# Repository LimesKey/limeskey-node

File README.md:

# parsnip-node
A battery-powered, portable Meshtastic/Meshcore node built around a Seeed XIAO ESP32-C6, an Ebyte E22P-915M30S LoRa front end, and a u-blox NEO-M9N GNSS receiver. Designed in KiCad, it targets 915 MHz operation in Canada under ISED RSS-247.

## Overview

The goal is a self-contained LoRa node that pairs one of the longest range, best value LoRa modules, with an accurate GNSS reciever, running off a single 18650 cell, to connect to other people on the LoRa mesh network community.

<table>
  <tr>
    <td align="center" width="33%">
      
      <br><sub><b>Assembled board</b></sub>
    </td>
    <td align="center" width="33%">
      
      <br><sub><b>Outdoor testing</b></sub>
    </td>
    <td align="center" width="33%">
      
      <br><sub><b>Outdoor testing, back</b></sub>
    </td>
  </tr>
</table>

## Hardware
 
| Function | Part | Notes |
| --- | --- | --- |
| MCU / radio host | Seeed XIAO ESP32-C6 | Used as an SMD/castellated module for easy soldering|
| LoRa | Ebyte E22P-915M30S | SX1262 + external PA, up to 30 dBm |
| GNSS | u-blox NEO-M9N | GPS / GLONASS / Galileo / BeiDou |
| Boost | TI TPS61033 |  |
| Power mux | TI TPS2116 | USB / battery source selection |
| Battery protection | TI BQ29700 | Single-cell protection |
| Reverse polarity | AO3401A P-channel MOSFET | Input protection |
| Cell | 18650 3500mAh Li-ion | Single cell |
 
### Board
 
- 4-layer, 55 x 100 mm
- JLCPCB `JLC04161H-7628` stackup, 1 oz copper
- L1-L2 prepreg 0.2104 mm, Dk 4.4
- RF: 0.36mm trace width for ~50 Ω CPWG on this stackup, ground rails stitched with 0.3 mm / 0.6 mm vias at roughly 1.5 to 2 mm pitch
  
### SX1262 to ESP32-C6 pin map
 
| Signal | GPIO |
| --- | --- |
| NSS | 21 |
| SCK | 19 |
| MISO | 20 |
| MOSI | 18 |
| DIO1 | 1 |
| BUSY | 7 |
| NRST | 16 |
| EN | 17 |
 
The E22P `EN` (module pin 6) is held high for both RX and TX. The T/R switch (pin 7) is driven automatically from the SX1262 DIO2 line, so the firmware sets `setDio2AsRfSwitch(true)`.
 
## Firmware
 
Firmware is a Meshtastic fork tracked as the `firmware` submodule ([LimesKey/firmware](https://github.com/LimesKey/firmware)). Development uses VS Code with the pioarduino extension, which Meshtastic pins for ESP32-C6 / Arduino-ESP32 3.x support. A device variant declares the pin map above and the PA control lines so TX actually keys up. Unfortunately there are some extensive changes to the Meshtastic firmware in order to incorporate a SPI GNSS module, as this is not natively supported by Meshtastic.
 
```bash
git clone --recurse-submodules https://github.com/LimesKey/parsnip-node.git
```

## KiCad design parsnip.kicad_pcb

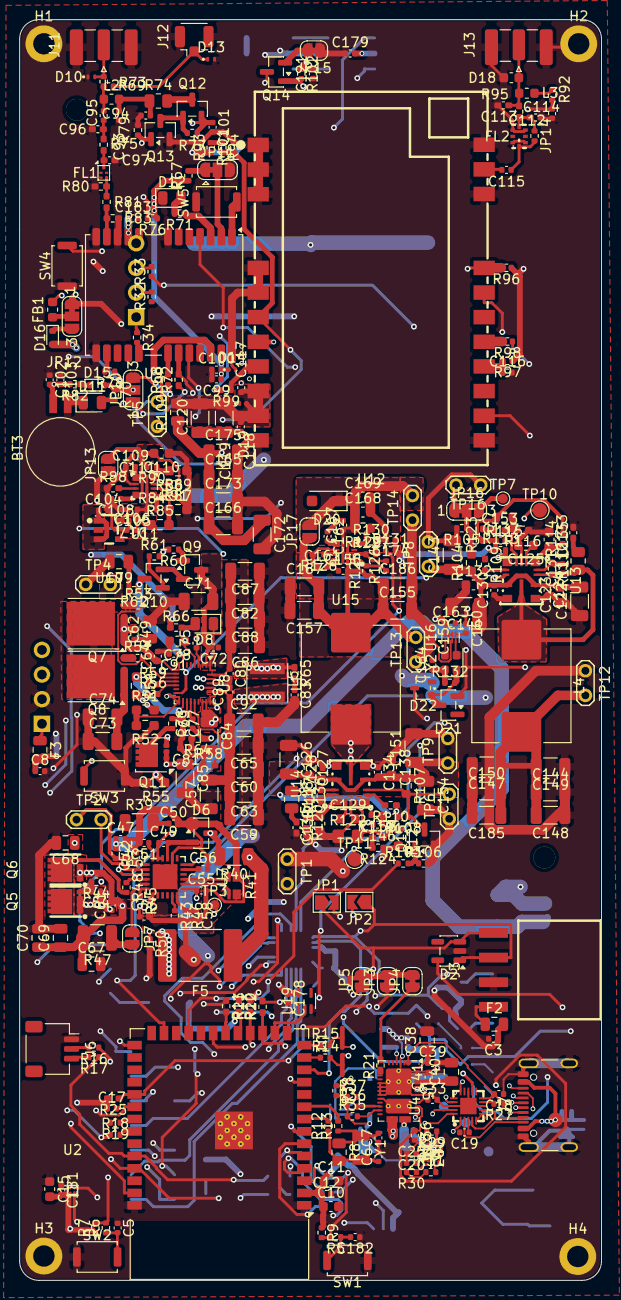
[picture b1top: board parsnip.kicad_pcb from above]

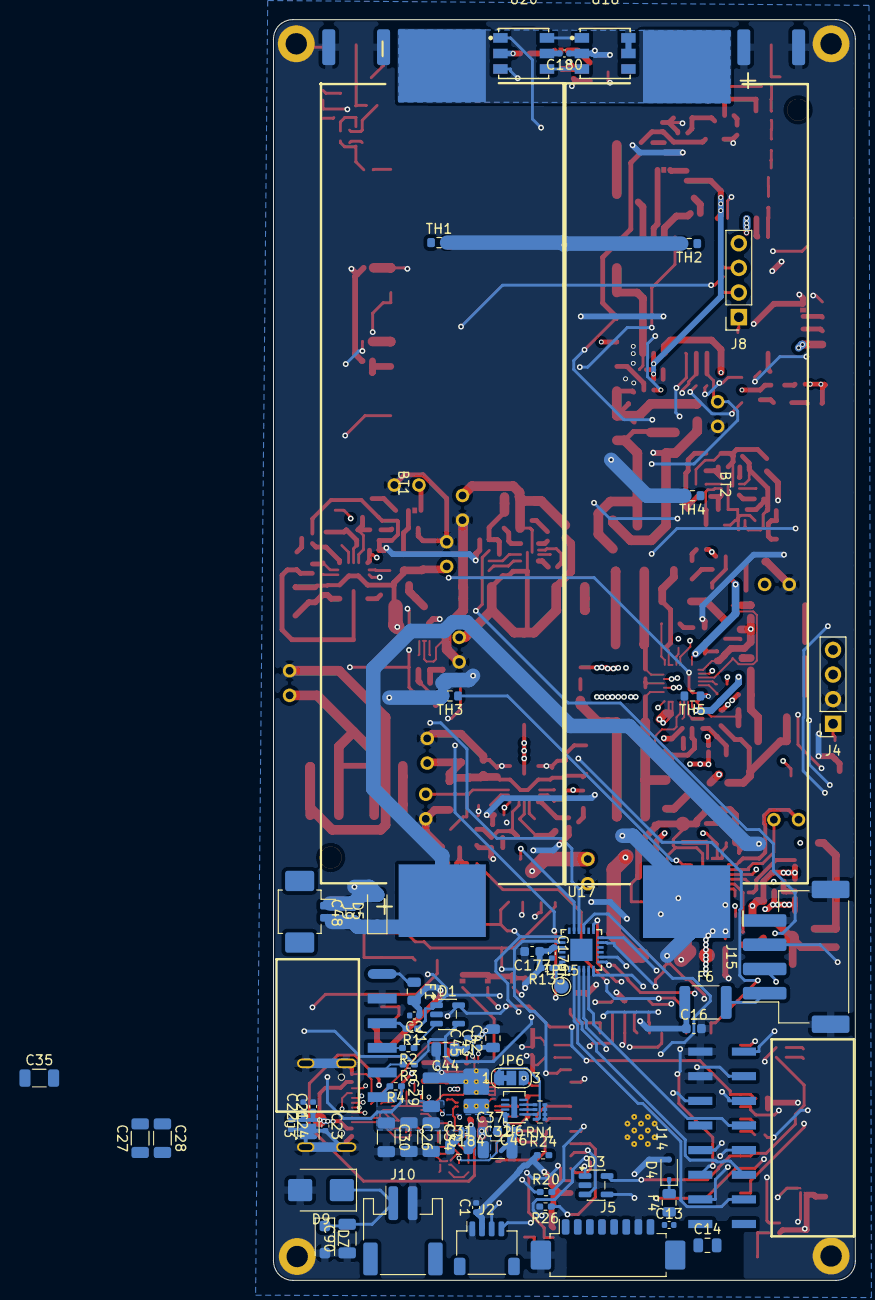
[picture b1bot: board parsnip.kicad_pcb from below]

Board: 4 copper layers, 60.0 x 130.0 mm, 450 parts (71 on the bottom side), 261 nets.

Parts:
BT1, BT2: 21700 Li-ion; BAT-SMD_L82.5.5-W25-BH-21700-B1BJ001
BT3: MS621FE 5.5mAh; BatteryHolder_Seiko_MS621F
C1, C2, C3, C8, C13, C104, C105: 2.2uF; C_0402_1005Metric
C5, C19, C24, C49, C50, C51, C54, C61, C64, C66, C72, C80, C89, C91, C116, C121, C124, C128, C130, C131, C134, C136, C184: 100nF; C_0402_1005Metric
C6, C7: 7pF; C_0402_1005Metric
C10, C11, C15, C16, C110, C168, C169, C177: 10uF; C_0603_1608Metric
C12, C17, C18, C20, C25, C39, C41, C43, C45, C46, C47, C52, C94, C100, C117, C118, C137, C146, C156, C163, C164, C167, C174, C176, C178, C179, C180, C181, C182, C183: 1uF; C_0402_1005Metric
C14, C38, C40, C42, C44, C48, C67, C68, C69, C70: 10uF; C_0805_2012Metric
C21, C22, C23: 10nF; C_0402_1005Metric
C26, C27, C28, C29, C30, C32, C34, C35, C57, C59, C60, C63, C65, C71, C73, C74, C82, C84, C85, C86, C87, C88, C90, C92, C122, C126, C141, C143, C151, C154: 10uF; C_1206_3216Metric
C31: 4.7uF; C_0805_2012Metric
C33, C36: 330pF; C_0402_1005Metric
C37, C123, C127, C132, C138: 1uF; C_0603_1608Metric
C53, C55, C56, C58: 0.47uF; C_0402_1005Metric
C62, C79: 2.2uF; C_0805_2012Metric
C75, C76, C77: 47nF; C_0402_1005Metric
C78: 4.7uF; C_0603_1608Metric
C81, C83: 1nF; C_0402_1005Metric_Pad0.74x0.62mm_HandSolder
C93: 22pF; C_0402_1005Metric
C95, C115: 47pF; C_0402_1005Metric
C96, C97: 10nF; C_0402_1005Metric_Pad0.74x0.62mm_HandSolder
C99, C102, C103, C106, C111: 10uF; C_0402_1005Metric
C101: 4.7uF; C_0402_1005Metric
C108, C109, C161, C162: 2.2nF; C_0402_1005Metric
C112, C159, C160: 1nF; C_0402_1005Metric
C113, C114: 1pF; C_0402_1005Metric_Pad0.74x0.62mm_HandSolder
C119, C120, C144, C147, C148, C149, C150, C155, C157, C165, C166, C172, C173, C175, C185, C186, C187: 22uF; C_1206_3216Metric
C125, C129, C135, C145: 2.2uF; C_0603_1608Metric
C133, C139: 220pF; C_0402_1005Metric_Pad0.74x0.62mm_HandSolder
C153, C158: 5.6pF; C_0402_1005Metric_Pad0.74x0.62mm_HandSolder
D1, D2, D3: ESDS314DBVR; SOT-23-5
D4: 1N5819WS; D_SOD-323
D5: SMF10A; D_SOD-123
D6: BAV199; SOT-23
D7: SMF24A; D_SOD-123F
D8: CHARGING; LED_0805_2012Metric
D9: SS36B; D_SMB
D10: TI ESD501; Texas_DPY0002A_0.6x1mm_P0.65mm
D11: LED Red; LED_0805_2012Metric
D12: LED Blue; LED_0805_2012Metric
D13: ESD501; Texas_DPY0002A_0.6x1mm_P0.65mm
D14: ESD351DPYR; Texas_DPY0002A_0.6x1mm_P0.65mm
D15: RB531SM-30; D_SOD-523
D16: RB531SM-30T2R; D_SOD-523
D17, D19: TPD1E10B06; Texas_DPY0002A_0.6x1mm_P0.65mm
D18: PGB1010603; C_0603_1608Metric
D20: SMF6.0A; D_SOD-123F
D21: BAT54A; SOT-23
D22: BAT54W; SOT-323_SC-70
F1, F3: 1A Hold; Fuse_0805_2012Metric
F2: 2A Hold, 4A Trip; Fuse_0805_2012Metric
F4: SMD0805B035TF; Fuse_0805_2012Metric
F5: 10A hold; Fuse_2920_7451Metric
F6: 3A hold 5A trip; Fuse_1812_4532Metric
FB1: BLM18HG601SN1D; L_0603_1608Metric
FL1: B39162B4327P810; Filter_1411-5_1.4x1.1mm
FL2: 0900LP15B0063001E; FILTER-SMD_0805-8P-L2.0-W1.2-TL
H1, H2, H3, H4: MountingHole_Pad; MountingHole_2.2mm_M2_DIN965_Pad
J1: SPI BUS; HDR-SMD_6P-P2.54-H-F-W11.7
J2: I2C3; JST_SH_SM04B-SRSS-TB_1x04-1MP_P1.00mm_Horizontal
J3: I2C1; CONN-SMD_4P-P2.54_HX-PM2.54-1X4PWT
J4: I2C2; PinSocket_1x04_P2.54mm_Vertical
J5: e-Ink Display Connector; Molex_PicoBlade_53261-0871_1x08-1MP_P1.25mm_Horizontal
J6: UART0; JST_SH_SM03B-SRSS-TB_1x03-1MP_P1.00mm_Horizontal
J7: GCT USB4105-GF-A-120; USB_C_Receptacle_GCT_USB4105-xx-A_16P_TopMnt_Horizontal
J8: PD_I2C DEBUG; PinSocket_1x04_P2.54mm_Vertical
J9: BAT_PORT; Molex_PicoBlade_53261-0271_1x02-1MP_P1.25mm_Horizontal
J10: SOLAR; JST_PH_S2B-PH-SM4-TB_1x02-1MP_P2.00mm_Horizontal
J11, J13: Conn_Coaxial; SMA_Samtec_SMA-J-P-H-ST-EM1_EdgeMount
J12: Conn_Coaxial_Small; U.FL_Hirose_U.FL-R-SMT-1_Vertical
J14: GPIO_Expander; HDR-SMD_16P-P2.54_HXPM2.54-2X8PWT
J15: LED 5V; JST_XH_S4B-XH-SM4-TB_1x04-1MP_P2.50mm_Horizontal
JP1, JP2: SolderJumper_2_Open; SolderJumper-2_P1.3mm_Open_TrianglePad1.0x1.5mm
JP3: I2C_IRQ_PULLUP; SolderJumper-2_P1.3mm_Bridged_RoundedPad1.0x1.5mm
JP4: I2C_SDA_PULLUP; SolderJumper-2_P1.3mm_Bridged_RoundedPad1.0x1.5mm
JP5: I2C_SCL_PULLUP; SolderJumper-2_P1.3mm_Bridged_RoundedPad1.0x1.5mm
JP6: WRITE_PROTECT; SolderJumper-3_P1.3mm_Bridged12_RoundedPad1.0x1.5mm_NumberL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
JP7: ZVC; SolderJumper-2_P1.3mm_Open_RoundedPad1.0x1.5mm
JP10: SolderJumper_3_Open; SolderJumper-3_P1.3mm_Open_RoundedPad1.0x1.5mm_NumberLabels
JP11: I2C/UART/SPI; SolderJumper-3_P1.3mm_Bridged12_RoundedPad1.0x1.5mm
JP12, JP16: SolderJumper_3_Bridged12; SolderJumper-3_P1.3mm_Bridged12_RoundedPad1.0x1.5mm_NumberL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
JP13: DISABLE_GNSS_PROT; SolderJumper-2_P1.3mm_Open_RoundedPad1.0x1.5mm
JP14: BYPASS_FILTER; R_0402_1005Metric
JP15: ANT_DETECT; SolderJumper-2_P1.3mm_Bridged_RoundedPad1.0x1.5mm
JP17: DISABLE_5V_PROT; SolderJumper-2_P1.3mm_Open_RoundedPad1.0x1.5mm
L1: 2.2uH; L_Vishay_IFSC-1515AH_4x4x1.8mm
L2: 47nH; L_0603_1608Metric
L3: 470nH; L_0603_1608Metric
L4: 2.2uH; L_Sunlord_MWSA1003S
L5: 3.3uH 11A Sat; L_APV_APH1040
NT1, NT2: NetTie_3; NetTie-3_SMD_Pad0.5mm
Q1, Q3: CSD25480F3; Texas_PicoStar_DFN-3_0.69x0.60mm
Q2, Q4: CSD15380F3; Texas_PicoStar_DFN-3_0.69x0.60mm
Q5, Q6: AON7534; PQFN-8_L3.1-W3.1-P0.65-LS3.3-BL
Q7, Q8: CSD18512Q5B; VSONP-8-1EP_5x6_P1.27mm
Q9, Q10: SI2308; SOT-23
Q11: CSD17581Q3A; VSON-8_3.3x3.3mm_P0.65mm_NexFET
Q12: AO3401A; SOT-23
Q13: BSS138; SOT-23
Q14, Q15: 2N7002; SOT-23
R1, R2, R3, R4: 33; R_0402_1005Metric_Pad0.72x0.64mm_HandSolder
R5, R6, R12, R13, R14, R15, R18, R19, R32, R33, R34, R69, R73, R93: 0; R_0402_1005Metric
R7, R9, R35, R38, R46, R50, R67, R76, R92, R94, R97, R101, R113, R119, R132: 10k; R_0402_1005Metric
R8: 10M; R_0805_2012Metric
R10, R11: 22; R_0402_1005Metric_Pad0.72x0.64mm_HandSolder
R16, R17, R98: 22; R_0402_1005Metric
R20, R24, R25, R26, R133: 10k; R_0402_1005Metric_Pad0.72x0.64mm_HandSolder
R21, R22, R68, R72: 2.2k; R_0402_1005Metric_Pad0.72x0.64mm_HandSolder
R23: 100k; R_0402_1005Metric_Pad0.72x0.64mm_HandSolder
R27, R28, R30, R56, R77, R79, R86, R91, R96, R105, R106, R108, R130, R131: 100k; R_0402_1005Metric
R29, R31, R102: 1M; R_0402_1005Metric
R36, R37: 2.2k; R_0402_1005Metric
R39, R40: 150; R_1206_3216Metric
R41: 5m; R_Shunt_0805_2012Metric_Kelvin
R42, R114, R120: 10; R_0402_1005Metric
R43, R45, R71, R78, R99: 1k; R_0402_1005Metric
R44, R48, R59, R63, R103: 100; R_0402_1005Metric
R47: 330; R_1210_3225Metric
R49, R62: 2; R_0402_1005Metric
R51: 5.24k; R_0603_1608Metric_Pad0.98x0.95mm_HandSolder
R52: 30.31k; R_0603_1608Metric_Pad0.98x0.95mm_HandSolder
R53, R57, R60, R61: 294; R_0402_1005Metric
R54: 24.3k; R_0603_1608Metric_Pad0.98x0.95mm_HandSolder
R55: 68.1k; R_0603_1608Metric_Pad0.98x0.95mm_HandSolder
R58: 8.2k; R_0402_1005Metric_Pad0.72x0.64mm_HandSolder
R64, R65: 2.2; R_0402_1005Metric_Pad0.72x0.64mm_HandSolder
R66: 3k; R_0402_1005Metric_Pad0.72x0.64mm_HandSolder
R70: 2k; R_0402_1005Metric
R74: 62; R_0805_2012Metric
R75, R95: 0; R_0402_1005Metric_Pad0.72x0.64mm_HandSolder
R80, R83: 150; R_0402_1005Metric_Pad0.72x0.64mm_HandSolder
R81: 37.4; R_0402_1005Metric_Pad0.72x0.64mm_HandSolder
R82: 4.7k; R_0402_1005Metric
R84: 150k; R_0402_1005Metric
R85: 215k; R_0603_1608Metric_Pad0.98x0.95mm_HandSolder
R87: 113k; R_0603_1608Metric_Pad0.98x0.95mm_HandSolder
R88: 6.65k; R_0402_1005Metric_Pad0.72x0.64mm_HandSolder
R89: 200k; R_0603_1608Metric_Pad0.98x0.95mm_HandSolder
R90: 301k; R_0402_1005Metric
R100: 0; R_0805_2012Metric
R104, R107, R115, R121: 402k; R_0603_1608Metric
R109, R110: 6.04k; R_0402_1005Metric_Pad0.72x0.64mm_HandSolder
R111, R117: 100; R_0402_1005Metric_Pad0.72x0.64mm_HandSolder
R112, R118: 2.2; R_0805_2012Metric
R116: 174k; R_0402_1005Metric_Pad0.72x0.64mm_HandSolder
R122: 101k; R_0805_2012Metric_Pad1.20x1.40mm_HandSolder
R123, R124: 1k; R_0402_1005Metric_Pad0.72x0.64mm_HandSolder
R125: 86.6k; R_0402_1005Metric
R126: 3.92k; R_0402_1005Metric
R127: 27.4k; R_0402_1005Metric
R128: 750; R_0402_1005Metric_Pad0.72x0.64mm_HandSolder
R129: 280k; R_0603_1608Metric
RN1: 10k; R_Array_Concave_4x0402
SW1: ESP_RESET; SW_Push_SPST_NO_Alps_SKRK
SW2: BOOT; SW_Push_SPST_NO_Alps_SKRK
SW3: POWER/RESET; SW_Push_SPST_NO_Alps_SKRK
SW4: RESET_GNSS; SW_Push_SPST_NO_Alps_SKRK
SW5: SAFEBOOT_GNSS; SW_Push_SPST_NO_Alps_SKRK
TH1, TH2, TH3, TH4, TH5: 103AT 10k; R_0603_1608Metric
TP1: R_SENSE_SHUNT; TestPoint_2Pads_Pitch2.54mm_Drill0.8mm
TP2: IN_CP; TestPoint_2Pads_Pitch2.54mm_Drill0.8mm
TP3: REG3; TestPoint_Pad_D1.0mm
TP4: PPHV; TestPoint_2Pads_Pitch2.54mm_Drill0.8mm
TP5: CS_GPS; TestPoint_2Pads_Pitch2.54mm_Drill0.8mm
TP6: SYNC_1; TestPoint_2Pads_Pitch2.54mm_Drill0.8mm
TP7: EN_3V3; TestPoint_Pad_D1.0mm
TP8, TP9: VSYS; TestPoint_2Pads_Pitch2.54mm_Drill0.8mm
TP10, TP11: PGOOD; TestPoint_Pad_D1.5mm
TP12: 3V3; TestPoint_2Pads_Pitch2.54mm_Drill0.8mm
TP13: 5V_RAW; TestPoint_2Pads_Pitch2.54mm_Drill0.8mm
TP14: 5V; TestPoint_2Pads_Pitch2.54mm_Drill0.8mm
TP15: GPIO_EXP_RESET; TestPoint_Pad_D1.5mm
TP16: SYNC_2; TestPoint_2Pads_Pitch2.54mm_Drill0.8mm
U1: ESP32-S3-WROOM-1-N16R8; ESP32-S3-WROOM-1
U2: QMC6309; X1-WLB0808-4_L0.8-W0.8-P0.40-TL
U3: TVS2200DRV; WSON-6-1EP_2x2mm_P0.65mm_EP1x1.6mm
U4: TPD8S300/A; WQFN-20_L3.0-W3.0-P0.40-TL-EP1.7
U5: TI TPS25751DREFR; Texas_REF0038A_WQFN-38-2EP_6x4mm_P0.4
U6: CAT24C256; DFN-8-1EP_2x3mm_P0.5mm_EP0.61x2.2mm
U7: MAX17320G22+; QFN-24_L4.0-W4.0-P0.50-BL-EP2.6
U8: BQ25798; Texas_RQM0029A_VQFN-29_4x4mm_P0.4mm
U9: NEO-M9N; ublox_NEO
U10: TPS7A2033PDBVR; SOT-23-5_L2.9-W1.6-P0.95-LS2.8-BR
U11: TPS259474LRPWR; VQFN-10_L2.0-W2.0-P0.45-TL
U12: E22P-915M30S; COMM-SMD_22P-P2.54-L38.5-W24.0_E22-400M33S
U13, U14: LM61460AASQRJRRQ1; VQFN-14-HR_L4.0-W3.5-TL_LM61460AASQRJRRQ1
U15: TPS259474ARPWR; VQFN-10_L2.0-W2.0-P0.45-TL
U16: SN74LVC1G74; X2SON-8_1.4x1mm_P0.35mm
U17: TCAL9539RTWR; TQFN-24_L4.0-W4.0-P0.50-BL-EP2.3
U18, U20: WS2816B; LED-SMD_6P-L5.0-W5.0-TL
U19: SN74LV1T34DCK; SOT-353_SC-70-5
Y1: 32.768KHz; Crystal_SMD_3215-2Pin_3.2x1.5mm
Y2: SX1M4.000M10F30TNN; Oscillator_SMD_SiT_PQFN-4Pin_2.0x1.6mm

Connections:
3V3_GNSS: C99.1, C100.2, C110.2, C111.1, D14.1 (A1), D15.2 (A), JP10.2 (C), JP13.2 (B), R67.1, R70.1, R76.1, R90.2, R91.1, U9.23 (VCC), U11.6 (OUT)
+3V3: C1.1, C2.1, C3.1, C8.1, C10.1, C11.1, C12.1, C15.2, C17.1, C38.1, C39.1, C121.2, C137.1, C144.1, C146.1, C147.1, C148.2, C149.2, C150.2, C163.1, C164.1, C174.1, C176.1, C177.1, C181.2, C185.1, D4.2 (A), F1.2, F2.2, F3.2, J2.2, JP3.2 (B), JP4.2 (B), JP5.2 (B), JP13.1 (A), L4.2, R7.1, R9.1, R23.2, R24.2, R25.2, R50.2, R93.1, R96.1, R97.1, R102.1, R113.1, R114.2, R115.2, R119.1, R123.1, R131.2, R132.1, R133.2, TP12.2, U1.2 (3V3), U2.B1 (VDD), U5.38 (VIN_3V3), U16.6 (~CLR), U16.7 (~PRE), U16.8 (VCC), U17.21 (VCC), Y2.4 (VDD)
+5V: C16.1, C40.1, C41.1, C104.1, C165.1, C166.1, C167.1, C168.1, C169.1, C172.1, C173.1, C175.1, C178.1, C179.2, C180.1, D20.1 (A1), F6.1, JP12.1 (A), JP17.2 (B), R100.1, R129.2, TP14.2, U5.34 (PP5V), U10.1 (IN), U10.3 (EN), U15.6 (OUT), U18.2 (VCC), U19.5 (VCC), U20.2 (VCC)
+BATT: C54.1, C61.1, F5.2, Q5.1 (S), Q5.2 (S), Q5.3 (S)
+PACK: C61.2, C66.1, C67.1, C68.1, C69.1, C70.1, Q6.1 (S), Q6.2 (S), Q6.3 (S), Q11.5 (D), R45.2, R47.2, R63.2
-BATT: BT2.2 (-), C47.2, C48.2, C50.2, C51.2, C52.2, C55.2, C56.2, C58.2, C66.2, D5.2 (A2), D6.1 (A), J9.1, R41.1, R43.2, R46.2, TH1.2, TH2.2, TH3.2, TH4.2, TP1.1, U7.20 (GND), U7.25 (EP)
/Charger/PMID: C80.1, C82.2, C86.2, C87.2, C88.2, U8.29 (PMID)
/Charger/REGN: C78.1, R51.2, R54.2, U8.5 (REGN)
/Root/BOOT: R6.2, R7.2, U1.27 (IO0)
/Root/BUSY_DISPLAY: D3.3 (I/O2), J5.1, U1.5 (IO5)
/Root/CS_BUS: D1.5 (I/O4), R4.1, R25.1, U1.31 (IO38)
/Root/CS_DISPLAY: D2.4 (I/O3), J5.4, R24.1, U1.10 (IO17)
/Root/D/C_DISPLAY: D3.1 (I/O1), J5.3, U1.11 (IO18)
/Root/EN: R5.2, R9.2, U1.3 (EN)
/Root/GNSS/D_SEL: JP11.2 (C), U9.2 (D_SEL)
/Root/GNSS/LNA_EN: R78.2, U9.14 (LNA_EN)
/Root/GNSS/SCL/SPI_CLK: JP2.2 (B), R72.2, U9.19 (SCL/SPI_CLK)
/Root/GNSS/SDA/SPI_CS: JP1.2 (B), R68.2, TP5.2, U9.18 (SDA/~SPI_CS)
/Root/GNSS/VCC_RF: C183.1, D16.2 (A), U9.9 (VCC_RF)
/Root/GPIO_3: R71.1, U1.15 (IO3), U9.3 (TIMEPULSE)
/Root/GPIO_4: U1.4 (IO4), U12.13 (DIO1)
/Root/GPIO_10: R23.1, R96.2, U1.18 (IO10), U12.19 (NSS)
/Root/GPIO_14: U1.22 (IO14), U12.14 (BUSY)
/Root/GPIO_21: R103.1, U1.23 (IO21)
/Root/GPIO_39: R131.1, U1.32 (IO39), U15.3 (PG/AUXOFF)
/Root/GPIO_40: R19.1, U1.33 (IO40)
/Root/GPIO_41: R18.2, U1.34 (IO41)
/Root/GPIO_42: R91.2, U1.35 (IO42), U11.3 (PG/AUXOFF)
/Root/GPIO_46: U1.16 (IO46), U19.2 (A)
/Root/GPIO_47: D21.1, U1.24 (IO47)
/Root/GPIO_48: U1.25 (IO48), U9.4 (EXTINT)
/Root/LoRa/ANT_DETECT: C112.2, Q14.1 (G), R92.1, R102.2
/Root/LoRa/EN: R18.1, R94.2, R101.1, U12.6 (EN)
/Root/LoRa/LORA_ANT: C115.1, U12.21 (ANT)
/Root/LoRa/RESET: C116.1, R19.2, R97.2, U12.15 (NRST)
/Root/P16: D21.2, R113.2, TP10.1 (1_1), U13.5 (PGOOD), U17.16
/Root/P17: D22.3 (K), R119.2, TP11.1 (1_1), U14.5 (PGOOD), U17.17
/Root/Peripherals/LED_BDO: J15.3, U20.1 (BO)
/Root/Peripherals/LED_DO: J15.2, U20.3 (DO)
/Root/Peripherals/P00: J14.1, U17.1 (P00)
/Root/Peripherals/P01: J14.3, U17.2 (P01)
/Root/Peripherals/P02: J14.5, U17.3 (P02)
/Root/Peripherals/P03: J14.7, U17.4 (P03)
/Root/Peripherals/P04: J14.9, U17.5 (P04)
/Root/Peripherals/P05: J14.11, U17.6 (P05)
/Root/Peripherals/P06: J14.13, U17.7 (P06)
/Root/Peripherals/P07: J14.15, U17.8 (P07)
/Root/Peripherals/P10: J14.2, U17.10
/Root/Peripherals/P11: J14.4, U17.11
/Root/Peripherals/P12: J14.6, U17.12
/Root/Peripherals/P13: J14.8, U17.13
/Root/Peripherals/P14: J14.10, U17.14
/Root/Peripherals/P15: J14.12, U17.15
/Root/Peripherals/RESET_IOEXP: R133.1, TP15.1 (1_1), U17.24 (~RESET)
/Root/RESET_DISPLAY: D2.5 (I/O4), J5.2, R26.1, U1.6 (IO6)
/Root/Rails/5V_RAW: C155.1, C156.2, C157.1, C186.1, C187.2, JP17.1 (A), L5.2, R120.2, R121.2, R124.1, R125.1, TP13.2, U15.5 (IN)
/Root/Rails/SYNC_1: C159.1, Q15.3 (D), R107.2, R108.1, TP6.2, U14.7 (EN/SYNC)
/Root/Rails/SYNC_2: C160.1, JP16.1 (A), TP16.2, U13.7 (EN/SYNC)
/USB Interface/CC1: C36.1, U4.12 (CC1), U5.28 (CC1)
/USB Interface/CC2: C33.1, U4.11 (CC2), U5.29 (CC2)
/USB Interface/C_CC1: J7.A5 (CC1), U4.4 (C_CC1), U4.7 (RPD_G1)
/USB Interface/C_CC2: J7.B5 (CC2), U4.5 (C_CC2), U4.6 (RPD_G2)
/USB Interface/C_SBU1: J7.A8 (SBU1), U4.1 (C_SBU1)
/USB Interface/C_SBU2: J7.B8 (SBU2), U4.2 (C_SBU2)
/USB Interface/FAULT: R27.2, U4.9 (~FLT), U5.19 (GPIO3)
/USB Interface/GPIO2: Q1.1 (G), Q2.1 (G), Q3.1 (G), Q4.1 (G), U5.7 (GPIO2)
/USB Interface/SBU1: R28.2, R29.1, U4.15 (SBU1), U5.26 (GPIO4/USB_P/LD1)
/USB Interface/SBU2: R30.2, R31.1, U4.14 (SBU2), U5.27 (GPIO5/USB_N/LD2)
/USB Interface/WC: JP6.2 (C), U6.7 (WP)
C_USB_B_N: J7.B7 (D-), NT1.3, U4.16 (D4)
C_USB_B_P: J7.B6 (D+), NT2.3, U4.17 (D3)
C_USB_T_N: J7.A7 (D-), NT1.1, U4.19 (D2)
C_USB_T_P: J7.A6 (D+), NT2.1, U4.20 (D1)
GND: BT3.2 (-), C1.2, C2.2, C3.2, C5.1, C6.2, C7.1, C8.2, C10.2, C11.2, C12.2, C13.2, C14.2, C15.1, C16.2, C17.2, C18.1, C19.2, C20.2, C21.2, C22.2, C23.2, C24.2, C25.1, C26.2, C27.2, C28.1, C29.2, C30.2, C31.1, C32.2, C33.2, C34.2, C35.2, C36.2, C37.2, C38.2, C39.2, C40.2, C41.2, C42.2, C43.2, C44.2, C45.2, C46.1, C57.1, C59.1, C60.1, C62.2, C63.1, C64.2, C65.1, C67.2, C68.2, C69.2, C70.2, C71.1, C72.1, C73.1, C74.1, C77.2, C78.2, C79.2, C80.2, C81.2, C82.1, C83.2, C84.2, C85.2, C86.1, C87.1, C88.1, C89.2, C90.1, C91.2, C92.2, C93.2, C94.2, C96.2, C97.2, C99.2, C100.1, C101.2, C102.1, C103.1, C104.2, C105.2, C106.1, C108.2, C109.1, C110.1, C111.2, C112.1, C113.2, C114.2, C116.2, C117.2, C118.2, C119.2, C120.2, C121.1, C122.1, C123.1, C124.2, C125.2, C126.1, C127.1, C128.2, C129.2, C130.1, C132.1, C133.2, C134.1, C135.1, C137.2, C138.1, C139.2, C141.2, C143.2, C144.2, C145.1, C146.2, C147.2, C148.1, C149.1, C150.1, C151.2, C154.2, C155.2, C156.1, C157.2, C161.1, C162.1, C163.2, C164.2, C165.2, C166.2, C167.2, C168.2, C169.2, C172.2, C173.2, C174.2, C175.2, C176.2, C177.2, C178.2, C179.1, C180.2, C181.1, C182.1, C183.2, C184.2, C185.2, C186.2, C187.1, D1.2 (GND), D2.2 (GND), D3.2 (GND), D7.2 (A2), D9.2 (A), D10.1 (A1), D11.1 (K), D12.1 (K), D13.2 (A2), D14.2 (A2), D17.2 (A2), D18.1 (A1), D19.1 (A1), D20.2 (A2), FL1.2, FL1.3, FL1.5, FL2.1 (GND), FL2.3 (GND), FL2.5 (GND), FL2.7 (GND), H1.1 (1_1), H2.1 (1_1), H3.1 (1_1), H4.1 (1_1), J1.2, J2.1, J3.2, J4.2, J5.7, J5.MP (MountPin), J6.1, J7.A1 (GND), J7.A12 (GND), J7.B1 (GND), J7.B12 (GND), J7.SH (SHIELD), J10.2, J11.2 (Ext), J12.2 (Ext), J13.2 (Ext), J14.14, J14.16, J15.4, J15.MP (MountPin), JP11.3 (B), JP15.1 (A), Q2.3 (S), Q4.3 (S), Q13.2 (S), Q15.2 (S), R26.2, R34.2, R41.4, R52.1, R55.2, R56.1, R58.1, R79.2, R80.1, R83.1, R86.2, R87.2, R88.1, R89.1, R101.2, R105.2, R106.2, R108.2, R109.1, R110.1, R116.1, R122.1, R127.2, R128.2, R130.2, RN1.1 (R1.1), RN1.2 (R2.1), RN1.3 (R3.1), RN1.4 (R4.1), SW1.1, SW2.1, SW3.1, SW4.1, SW5.1, TH5.2, TP1.2, TP4.1, TP5.1, TP6.1, TP8.2, TP9.2, TP12.1, TP13.1, TP14.1, TP16.1, U1.1 (GND), U1.40 (GND), U1.41 (GND), U2.A1 (VSS), U3.1 (GND), U3.2 (GND), U3.3 (GND), U3.7 (GND), U4.8 (GND), U4.13 (GND), U4.18 (GND), U4.21 (EP), U5.3 (ADCIN2), U5.5 (GPIO0), U5.11 (GND), U5.12 (GND), U5.13 (GPIO11), U5.14 (GND), U5.31 (GND), U5.36 (GPIO7), U5.37 (GPIO6), U5.39 (GND), U6.4 (GND), U8.27 (GND), U9.7 (VDD_USB), U9.10 (GND), U9.12 (GND), U9.13 (GND), U9.24 (GND), U10.2 (GND), U11.8 (GND), U12.1 (GND), U12.2 (GND), U12.3 (GND), U12.4 (GND), U12.5 (GND), U12.11 (GND), U12.12 (GND), U12.20 (GND), U12.22 (GND), U13.3 (AGND), U13.9 (PGND1), U13.11 (PGND2), U14.3 (AGND), U14.9 (PGND1), U14.11 (PGND2), U15.8 (GND), U16.4 (GND), U17.9 (GND), U17.18 (A0), U17.23 (A1), U17.25 (EP), U18.5 (GND), U18.6 (BI), U19.3 (GND), U20.5 (GND), Y2.2 (GND)
GPS_ANT: R81.2, R83.2, U9.11 (RF_IN)
I2C_HOST_IRQ: R20.1, U1.7 (IO7), U5.6 (GPIO1), U5.10 (~I2Ct_IRQ), U17.22 (~INT)
I2C_HOST_SCL: D2.1 (I/O1), J2.3, J3.3, J4.3, JP2.1 (A), R22.1, U1.17 (IO9), U2.A2 (SCL), U5.9 (I2Ct_SCL), U7.8 (SCL/DOD), U17.19 (SCL)
I2C_HOST_SDA: D2.3 (I/O2), J2.4, J3.4, J4.4, JP1.1 (A), R21.1, U1.12 (IO8), U2.B2 (SDA), U5.8 (I2Ct_SDA), U7.9 (SDA/DQ), U17.20 (SDA)
I2C_PMIC_IRQ: R35.2, U5.18 (~I2Cc_IRQ), U8.21 (~INT)
I2C_PMIC_SCL: R32.1, R36.2, U5.17 (I2Cc_SCL), U6.6 (SCL), U8.14 (SCL)
I2C_PMIC_SDA: R33.1, R37.2, U5.16 (I2Cc_SDA), U6.5 (SDA), U8.15 (SDA)
MISO: D1.4 (I/O3), R3.1, R98.1, U1.21 (IO13)
MOSI: D1.3 (I/O2), J5.6, R2.1, R10.1, U12.17 (MOSI)
unnamed: BT1.1 (+), C47.1, C48.1, D5.1 (A1), F5.1, J9.2, R40.1, R42.1
unnamed: BT1.2 (-), BT2.1 (+), R39.1
unnamed: BT3.1 (+), C102.2, C103.2, R82.2, U9.22 (V_BCKP)
unnamed: C5.2, R6.1, SW2.2
unnamed: C6.1, R8.2, R12.1, Y1.1
unnamed: C7.2, R8.1, R13.1, Y1.2
unnamed: C62.1, R49.2
unnamed: C79.1, R62.2
unnamed: C81.1, R64.2
unnamed: C83.1, R65.2
unnamed: C84.1, C85.1, Q11.1 (S), Q11.2 (S), Q11.3 (S), U8.22 (BAT), U8.23 (BAT)
unnamed: C93.1, C94.1, L2.2, R74.1
unnamed: C95.1, C96.1, R75.1
unnamed: C95.2, L2.1, R69.2, R73.2
unnamed: C97.1, FL1.1, R75.2
unnamed: C133.1, R112.2
unnamed: C139.1, R118.2
unnamed: C153.1, R123.2
unnamed: C158.1, R124.2
unnamed: C182.2, R5.1, SW1.2
unnamed: D4.1 (K), F4.2
unnamed: C49.1, C51.1, D6.3 (K), R40.2, U7.22 (CELL2), U7.23 (CELL3), U7.24 (BATTS)
unnamed: C49.2, C50.1, D6.2 (common), R39.2, U7.21 (CELL1)
unnamed: D8.2 (A), R66.2
unnamed: D8.1 (K), U8.1 (STAT)
unnamed: D10.2 (A2), J11.1 (In), R69.1
unnamed: D11.2 (A), R70.2
unnamed: D12.2 (A), R71.2
unnamed: D13.1 (A1), J12.1 (In), R73.1
unnamed: D15.1 (K), R82.1
unnamed: D16.1 (K), JP12.3 (B)
unnamed: C105.1, C106.2, D17.1 (A1), R84.1, R85.1, U10.5 (OUT), U11.5 (IN)
unnamed: C113.1, D18.2 (A2), J13.1 (In), L3.2, R95.1
unnamed: C117.1, C118.1, C119.1, C120.1, D19.2 (A2), R100.2, U12.9 (VCC), U12.10 (VCC)
unnamed: D21.3, D22.1 (A), R132.2, Y2.1 (~ST)
unnamed: FL1.4, R80.2, R81.1
unnamed: F1.1, J1.1
unnamed: J1.3, R1.2
unnamed: J1.4, R2.2
unnamed: J1.5, R3.2
unnamed: J1.6, R4.2
unnamed: F2.1, J3.1
unnamed: F3.1, J4.1
unnamed: C13.1, C14.1, F4.1, J5.8
unnamed: J6.2, R16.2
unnamed: J6.3, R17.2
unnamed: J8.1, R34.1
unnamed: J8.2, R32.2
unnamed: J8.3, R33.2
unnamed: F6.2, J15.1
unnamed: JP3.1 (A), R20.2
unnamed: JP4.1 (A), R21.2
unnamed: JP5.1 (A), R22.2
unnamed: JP6.1 (A), RN1.8 (R1.2)
unnamed: JP6.3 (B), R38.1
unnamed: JP7.1 (A), U7.5 (ZVC)
unnamed: JP7.2 (B), R47.1
unnamed: JP10.1 (A), R72.1
unnamed: JP10.3 (B), R68.1
unnamed: JP11.1 (A), R67.2
unnamed: FB1.2, JP12.2 (C)
unnamed: C114.1, FL2.4 (IO), JP14.1 (A), R95.2
unnamed: C115.2, FL2.8 (IO), JP14.2 (B)
unnamed: JP15.2 (B), Q14.2 (S)
unnamed: JP16.3 (B), TP7.1 (1_1)
unnamed: JP16.2 (C), R104.2, R105.1
unnamed: L3.1, R92.2
unnamed: Q1.3 (D), R28.1
unnamed: Q2.2 (D), R29.2
unnamed: Q3.3 (D), R30.1
unnamed: Q4.2 (D), R31.2
unnamed: Q5.5 (D), Q5.6 (D), Q5.7 (D), Q5.8 (D), Q6.5 (D), Q6.6 (D), Q6.7 (D), Q6.8 (D)
unnamed: C54.2, Q5.4 (G), R44.2
unnamed: Q6.4 (G), R48.2
unnamed: Q7.2 (G), R53.1
unnamed: Q7.3 (S), Q8.3 (S)
unnamed: C71.2, C72.2, C73.2, C74.2, Q8.1 (D), Q9.3 (D), U8.2 (VBUS), U8.3 (VBUS)
unnamed: Q8.2 (G), R57.1
unnamed: Q9.1 (G), R60.1
unnamed: Q10.1 (G), R61.1
unnamed: Q9.2 (S), Q10.2 (S)
unnamed: Q11.4 (G), U8.24 (SDRV)
unnamed: Q12.3 (D), R74.2
unnamed: Q12.1 (G), Q13.3 (D), R77.2
unnamed: C101.1, FB1.1, Q12.2 (S), R77.1
unnamed: Q13.1 (G), R78.1, R79.1
unnamed: Q14.3 (D), R99.2, U12.7 (T/RCTRL)
unnamed: Q15.1 (G), R103.2, R106.1
unnamed: R59.1, SW3.2
unnamed: R93.2, R94.1
unnamed: RN1.7 (R2.2), U6.1 (A0)
unnamed: RN1.6 (R3.2), U6.2 (A1)
unnamed: RN1.5 (R4.2), U6.3 (A2)
unnamed: R10.2, U1.19 (IO11)
unnamed: R11.2, U1.20 (IO12)
unnamed: R12.2, U1.8 (IO15)
unnamed: R13.2, U1.9 (IO16)
unnamed: R15.1, U1.14 (USB_D+)
unnamed: R14.1, U1.13 (USB_D-)
unnamed: C19.1, U4.3 (VBIAS)
unnamed: U5.15 (DRAIN), U5.30 (DRAIN), U5.40 (DRAIN)
unnamed: C42.1, C43.1, U5.4 (LDO_1V5)
unnamed: R50.1, U7.7 (ALRT)
unnamed: C58.1, R46.1, U7.12 (AOLDO)
unnamed: R44.1, U7.3 (CHG)
unnamed: C53.2, TP2.2, U7.2 (CP)
unnamed: R41.3, U7.14 (CSN)
unnamed: R41.2, U7.15 (CSP)
unnamed: R48.1, U7.4 (DIS)
unnamed: C52.1, C53.1, R42.2, TP2.1, U7.1 (IN)
unnamed: R45.1, U7.6 (PCKP)
unnamed: R43.1, U7.11 (PFALL)
unnamed: C56.1, U7.17 (REG2)
unnamed: C55.1, TP3.1 (1_1), U7.13 (REG3)
unnamed: TH4.1, U7.10 (TH1)
unnamed: TH1.1, U7.16 (TH2)
unnamed: TH3.1, U7.18 (TH3)
unnamed: TH2.1, U7.19 (TH4)
unnamed: R53.2, R57.2, U8.11 (ACDRV1)
unnamed: R60.2, R61.2, U8.10 (ACDRV2)
unnamed: C77.1, R63.1, U8.18 (BATP)
unnamed: C75.1, U8.4 (BTST1)
unnamed: C76.2, U8.19 (BTST2)
unnamed: R54.1, R55.1, U8.17 (ILIM_HIZ)
unnamed: R58.2, U8.20 (PROG)
unnamed: C75.2, L1.1, R65.1, U8.28 (SW1)
unnamed: C76.1, L1.2, R64.1, U8.26 (SW2)
unnamed: R51.1, R52.2, TH5.1, U8.16 (TS)
unnamed: R56.2, U8.13 (~CE)
unnamed: R59.2, U8.12 (~QON)
unnamed: R76.2, SW4.2, U9.8 (~RESET)
unnamed: SW5.2, U9.1 (~SAFEBOOT)
unnamed: C109.2, U11.7 (DVDT)
unnamed: R84.2, R86.1, U11.1 (EN/UVLO)
unnamed: R88.2, U11.9 (ILM)
unnamed: C108.1, U11.10 (ITIMER)
unnamed: R85.2, R87.1, U11.2 (OVLO/OVCSEL)
unnamed: R89.2, R90.1, U11.4 (PGTH/~FLT)
unnamed: R99.1, U12.8 (DIO2)
unnamed: R98.2, U12.16 (MISO)
unnamed: C135.2, R114.1, U13.1 (BIAS)
unnamed: C131.2, R111.1, U13.14 (CBOOT)
unnamed: C153.2, R115.1, R116.2, U13.4 (FB)
unnamed: R111.2, U13.13 (RBOOT)
unnamed: R109.2, U13.6 (RT)
unnamed: C131.1, L4.1, R112.1, U13.10 (SW)
unnamed: C125.1, U13.2 (VCC)
unnamed: C145.2, R120.1, U14.1 (BIAS)
unnamed: C136.2, R117.1, U14.14 (CBOOT)
unnamed: C158.2, R121.1, R122.2, U14.4 (FB)
unnamed: R117.2, U14.13 (RBOOT)
unnamed: R110.2, U14.6 (RT)
unnamed: C136.1, L5.1, R118.1, U14.10 (SW)
unnamed: C129.1, U14.2 (VCC)
unnamed: C162.2, U15.7 (DVDT)
unnamed: R125.2, R126.1, U15.1 (EN/UVLO)
unnamed: R128.1, U15.9 (ILM)
unnamed: C161.2, U15.10 (ITIMER)
unnamed: R126.2, R127.1, U15.2 (OVLO/OVCSEL)
unnamed: R129.1, R130.1, U15.4 (PGTH/~FLT)
unnamed: U16.1 (C), Y2.3 (OUT)
unnamed: C159.2, U16.2 (D), U16.3 (~Q)
unnamed: C160.2, U16.5 (Q)
unnamed: U18.1 (BO), U20.6 (BI)
unnamed: U18.4 (DI), U19.4 (Y)
unnamed: U18.3 (DO), U20.4 (DI)
PD_LDO_3V3: C18.2, C20.1, C25.2, C44.1, C45.1, C46.2, J8.4, Q1.2 (S), Q3.2 (S), R27.1, R35.1, R36.1, R37.1, R38.2, R66.1, U4.10 (VPWR), U5.1 (LDO_3V3), U5.2 (ADCIN1), U6.8 (VCC)
PPHV: C26.1, C27.1, C28.2, C29.1, C30.1, C32.1, C34.1, C35.1, C37.1, C64.1, Q7.1 (D), R49.1, TP4.2, U5.20 (PPHV), U8.9 (VAC1)
SCK: D1.1 (I/O1), J5.5, R1.1, R11.1, U12.18 (SCK)
SOLAR: C90.2, C91.1, D7.1 (A1), D9.1 (K), J10.1, Q10.3 (D), R62.1, U8.8 (VAC2)
UART0_RX: D3.5 (I/O4), R17.1, U1.36 (RXD0)
UART0_TX: D3.4 (I/O3), R16.1, U1.37 (TXD0)
UART1_RX: U1.39 (IO1), U9.20 (TXD/SPI_MISO)
UART1_TX: U1.38 (IO2), U9.21 (RXD/SPI_MOSI)
USB D+: NT2.2, R15.2
USB D-: NT1.2, R14.2
VBUS: C21.1, C22.1, C23.1, C24.1, C31.2, C184.1, J7.A4 (VBUS), J7.A9 (VBUS), J7.B4 (VBUS), J7.B9 (VBUS), U3.4 (IN), U3.5 (IN), U3.6 (IN), U5.23 (VBUS_IN), U5.32 (VBUS)
VSYS: C57.2, C59.2, C60.2, C63.2, C65.2, C89.1, C92.1, C122.2, C123.2, C124.1, C126.2, C127.2, C128.1, C130.2, C132.2, C134.2, C138.2, C141.1, C143.1, C151.1, C154.1, R104.1, R107.1, TP8.1, TP9.1, U8.25 (SYS), U13.8 (VIN1), U13.12 (VIN2), U14.8 (VIN1), U14.12 (VIN2)

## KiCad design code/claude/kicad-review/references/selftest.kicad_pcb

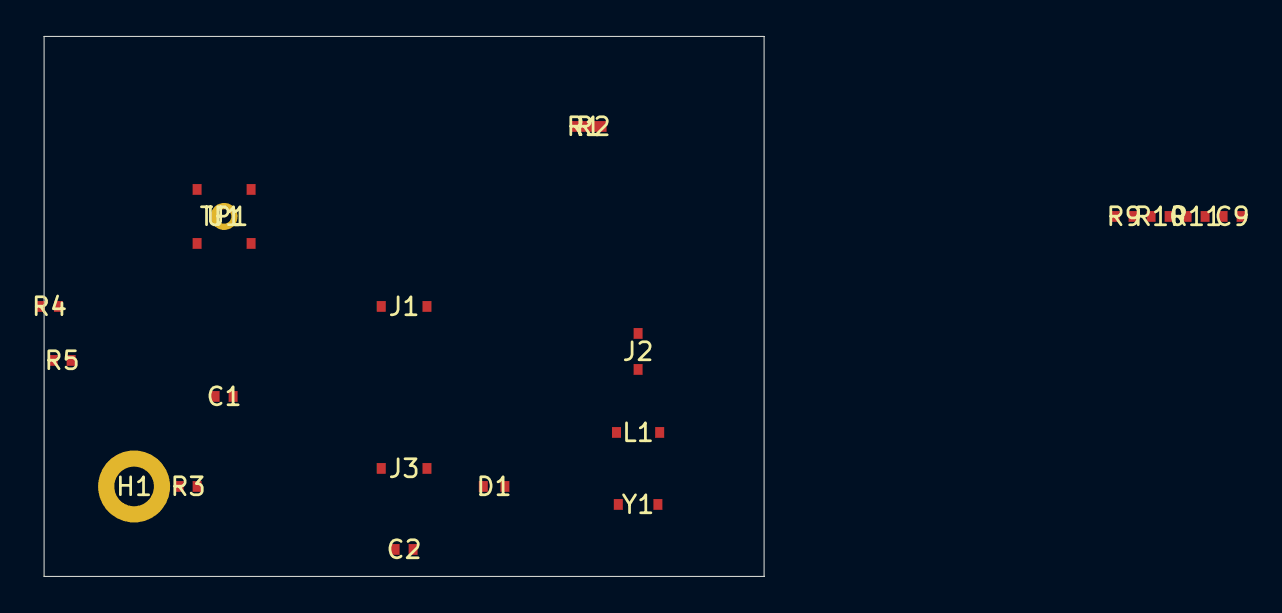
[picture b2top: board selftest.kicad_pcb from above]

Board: 2 copper layers, 40.0 x 30.0 mm, 20 parts (1 on the bottom side), 3 nets, no tracks yet.

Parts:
C1: 100nF; FP
C2: 1uF; FP
C9: 10k; FP
D1: LED; FP
H1: MountingHole; MountingHole_2.2mm_M2_DIN965_Pad
J1, J3: HDR; PinHeader_1x02_P2.54mm_Vertical
J2: Conn_Coaxial; U.FL_Hirose_U.FL-R-SMT-1_Vertical
L1: 2.2uH; L_4x4mm
R1, R2, R9, R10, R11: 10k; FP
R3: 1k; FP
R4, R5: 0R; FP
TP1: TP; TestPoint_Pad_D1.5mm
U1: MCU_OK; FP
Y1: 32.768kHz; Crystal_SMD_3215-2Pin_3.2x1.5mm

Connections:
+3V3: C1.1, U1.1 (VDD)
GND: C1.2, C2.2, D1.2, J2.2, TP1.1, U1.2 (GND)
NB: R1.2, R2.1

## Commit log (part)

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2026-06-01 inital commit
2026-06-16 commits for assembly
2026-06-18 show to ppl
2026-06-19 clean up repo
